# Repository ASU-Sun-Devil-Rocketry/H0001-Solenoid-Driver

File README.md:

<h1>Solenoid Driver</h1>

<p>Current PCB Revision: 1.0</p>
<p>PCB Part Number: H0001</p>

<p>The solenoid driver uses solid state relays to allow an Arduino Mega 
to control AC powered solenoids with a 5V control signal. The board is 
used by the SDR Hybrid Propulsion team to control their Pancake engine's 
pressurization and main oxidizer valves. </p>

<p><b>Working Directory Structure:</b></p>

<p>
   doc: documentation
   
   src: source design files, e.g. schematic and PCB layout files

   lib: libraries for schematic symbols and footprints

   production: files needed for pcb fabrication, e.g. gerbers, profile, drill file

   sim: simulation models/files 

   cad: 3d models
  
   img: images of circuit/footprints for github display 
</p>

<h2>3D Model: </h2>

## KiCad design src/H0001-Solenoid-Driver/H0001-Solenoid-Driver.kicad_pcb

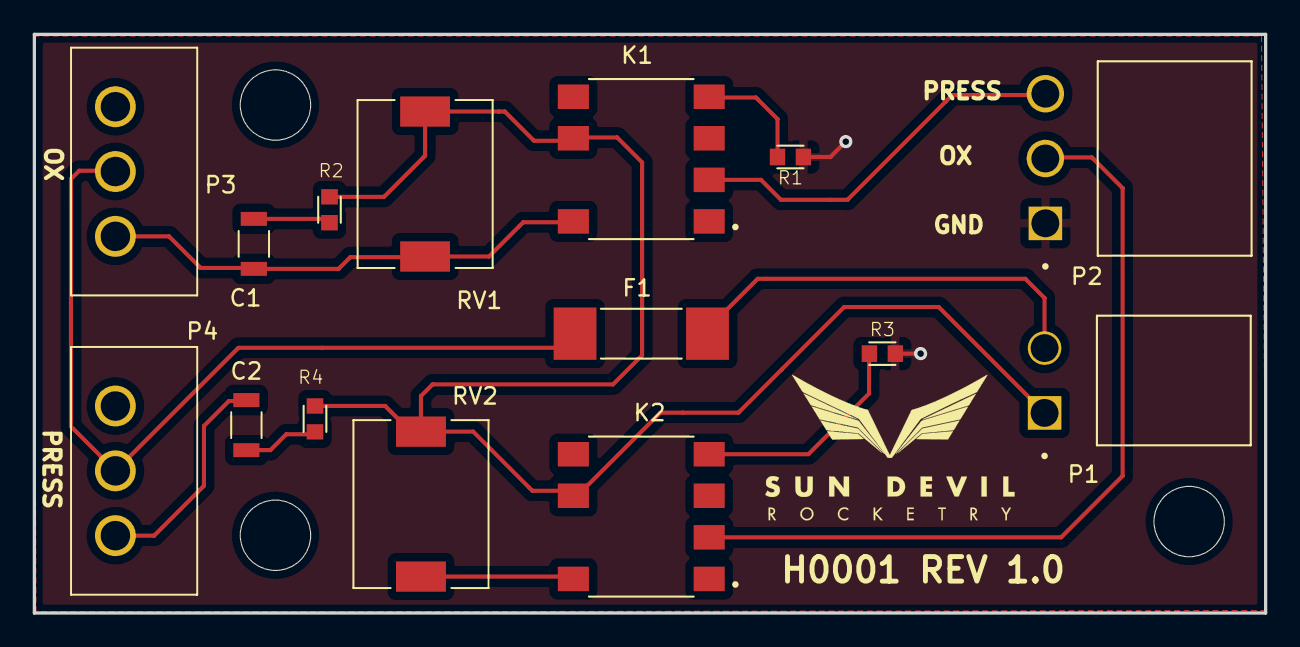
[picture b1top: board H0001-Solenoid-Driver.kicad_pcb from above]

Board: 2 copper layers, 75.2 x 35.4 mm, 19 parts (0 on the bottom side), 12 nets.

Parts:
C1, C2: 0.1uF; CAP_1206
F1: 0678L9100-02; FUSC9830X318N
H1, H2, H3: Mounting-Hole; MountingHole_4.3mm_M4_DIN965
K1, K2: AQH0223AX; RELAY_AQH0223AX
LOGO1: Logo
P1: 647676-2; TE_647676-2
P2: 647676-3
P3, P4: 647676-3; 353130360
R1, R3: 180; RES_0603
R2, R4: 100; RES_0603
RV1, RV2: 275V; PV275K4032R2

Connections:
AC_HOT: F1.2, P3.2, P4.2
AC_NEU: K1.6, K2.6, P1.1, R2.1, R4.1, RV1.2, RV2.2
Earth: P2.1, R1.1, R3.1
unnamed: C1.1, K1.8, P3.1, RV1.1
unnamed: C1.2, R2.2
unnamed: C2.1, K2.8, P4.1, RV2.1
unnamed: C2.2, R4.2
unnamed: F1.1, P1.2
unnamed: K1.4, R1.2
unnamed: K2.4, R3.2
OX: K2.2, P2.2
PRESS: K1.2, P2.3

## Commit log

2022-01-16 created directory structure
2022-01-16 Updated README description
2022-01-16 created initial symbol library
2022-01-16 created initial footprint library
2022-01-16 Added solid state relays to schematic
2022-01-16 added fuse to lib files
2022-01-16 Added connectors to schematic
2022-01-16 linked footprints with symbols
2022-01-16 Routed PCB
2022-01-16 Added 3D model to readme
2022-01-16 fixed missing image
2022-01-29 Added schematic images to readme
2022-01-29 plotted schematic to pdf
2022-06-30 minor local commits
